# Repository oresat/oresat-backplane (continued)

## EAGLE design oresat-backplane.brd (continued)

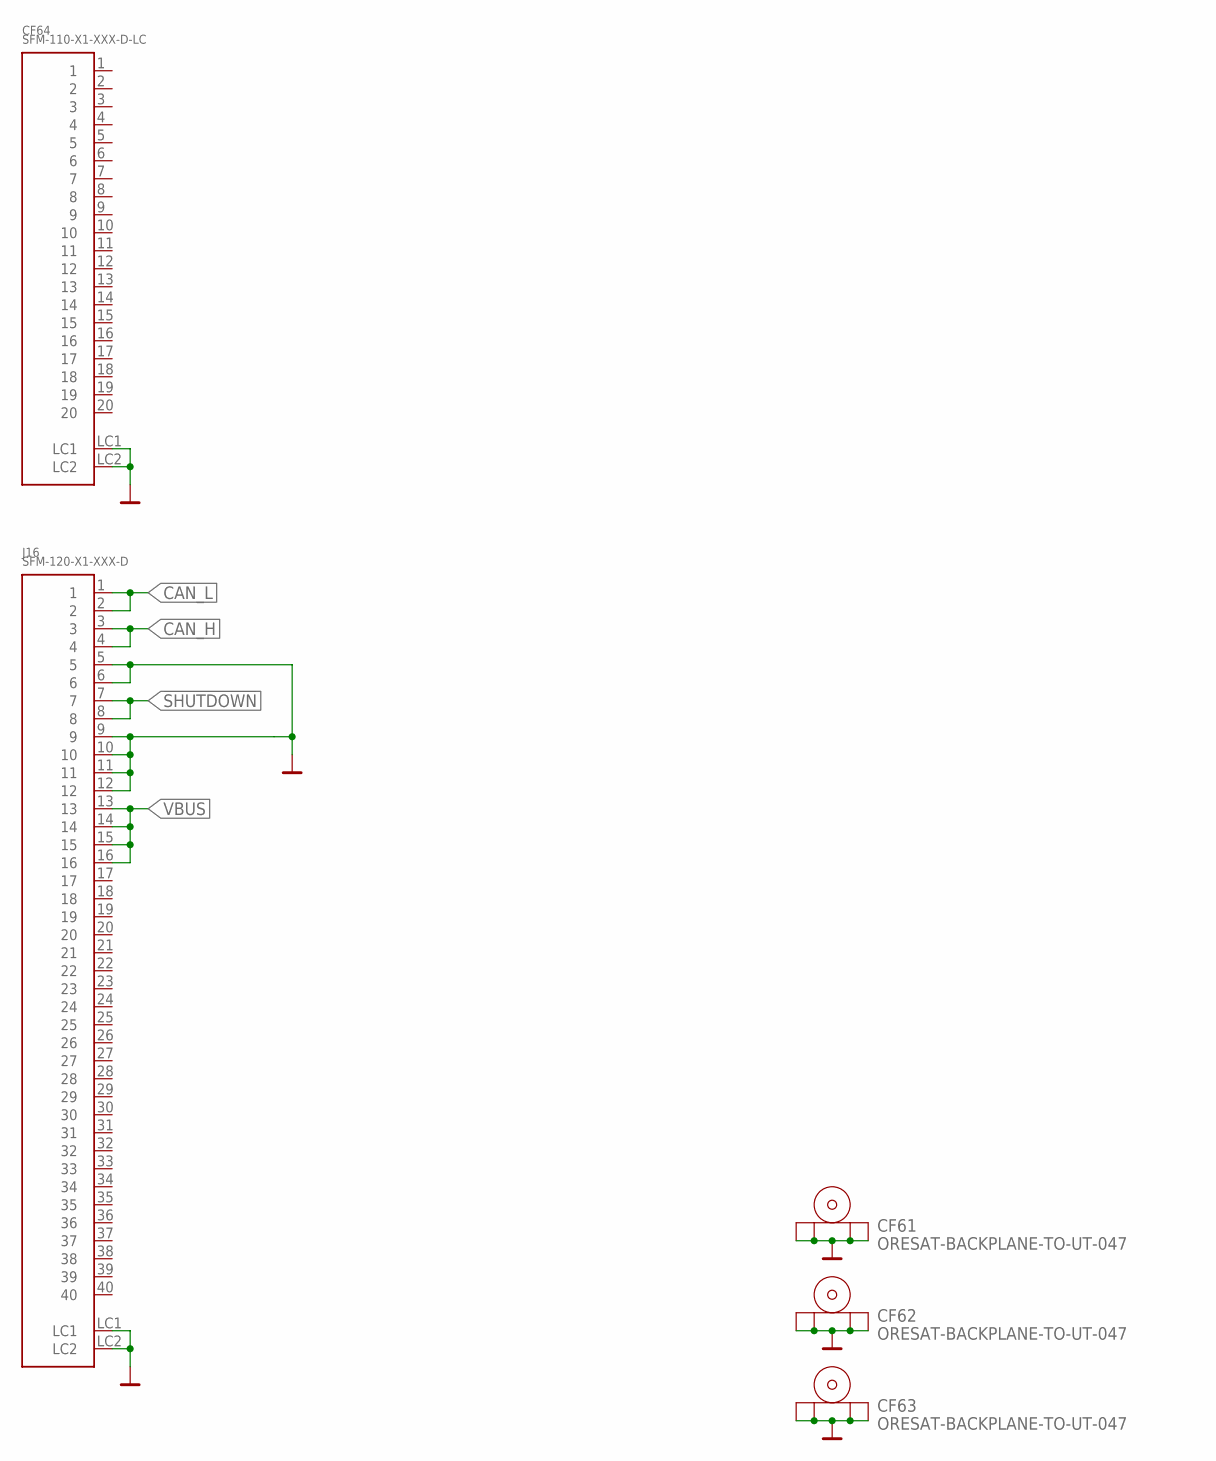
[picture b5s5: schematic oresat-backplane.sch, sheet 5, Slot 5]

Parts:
CF61, CF62, CF63: ORESAT-BACKPLANE-TO-UT-047; TEST
CF64: SFM-110-X1-XXX-D-LC
J16: SFM-120-X1-XXX-D

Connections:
!SHUTDOWN: J16.7, J16.8; also elsewhere on the board
CAN_H: J16.3, J16.4; also elsewhere on the board
CAN_L: J16.1, J16.2; also elsewhere on the board
GND: CF61.GND@1 (SHIELD), CF61.GND@2 (SHIELD1), CF61.GND@3 (SHIELD2), CF61.GND@4 (SHIELD3), CF62.GND@1 (SHIELD), CF62.GND@2 (SHIELD1), CF62.GND@3 (SHIELD2), CF62.GND@4 (SHIELD3), CF63.GND@1 (SHIELD), CF63.GND@2 (SHIELD1), CF63.GND@3 (SHIELD2), CF63.GND@4 (SHIELD3), CF64.LC1, CF64.LC2, J16.5, J16.6, J16.9, J16.10, J16.11, J16.12, J16.LC1, J16.LC2; also elsewhere on the board
VBUS: J16.13, J16.14, J16.15, J16.16; also elsewhere on the board

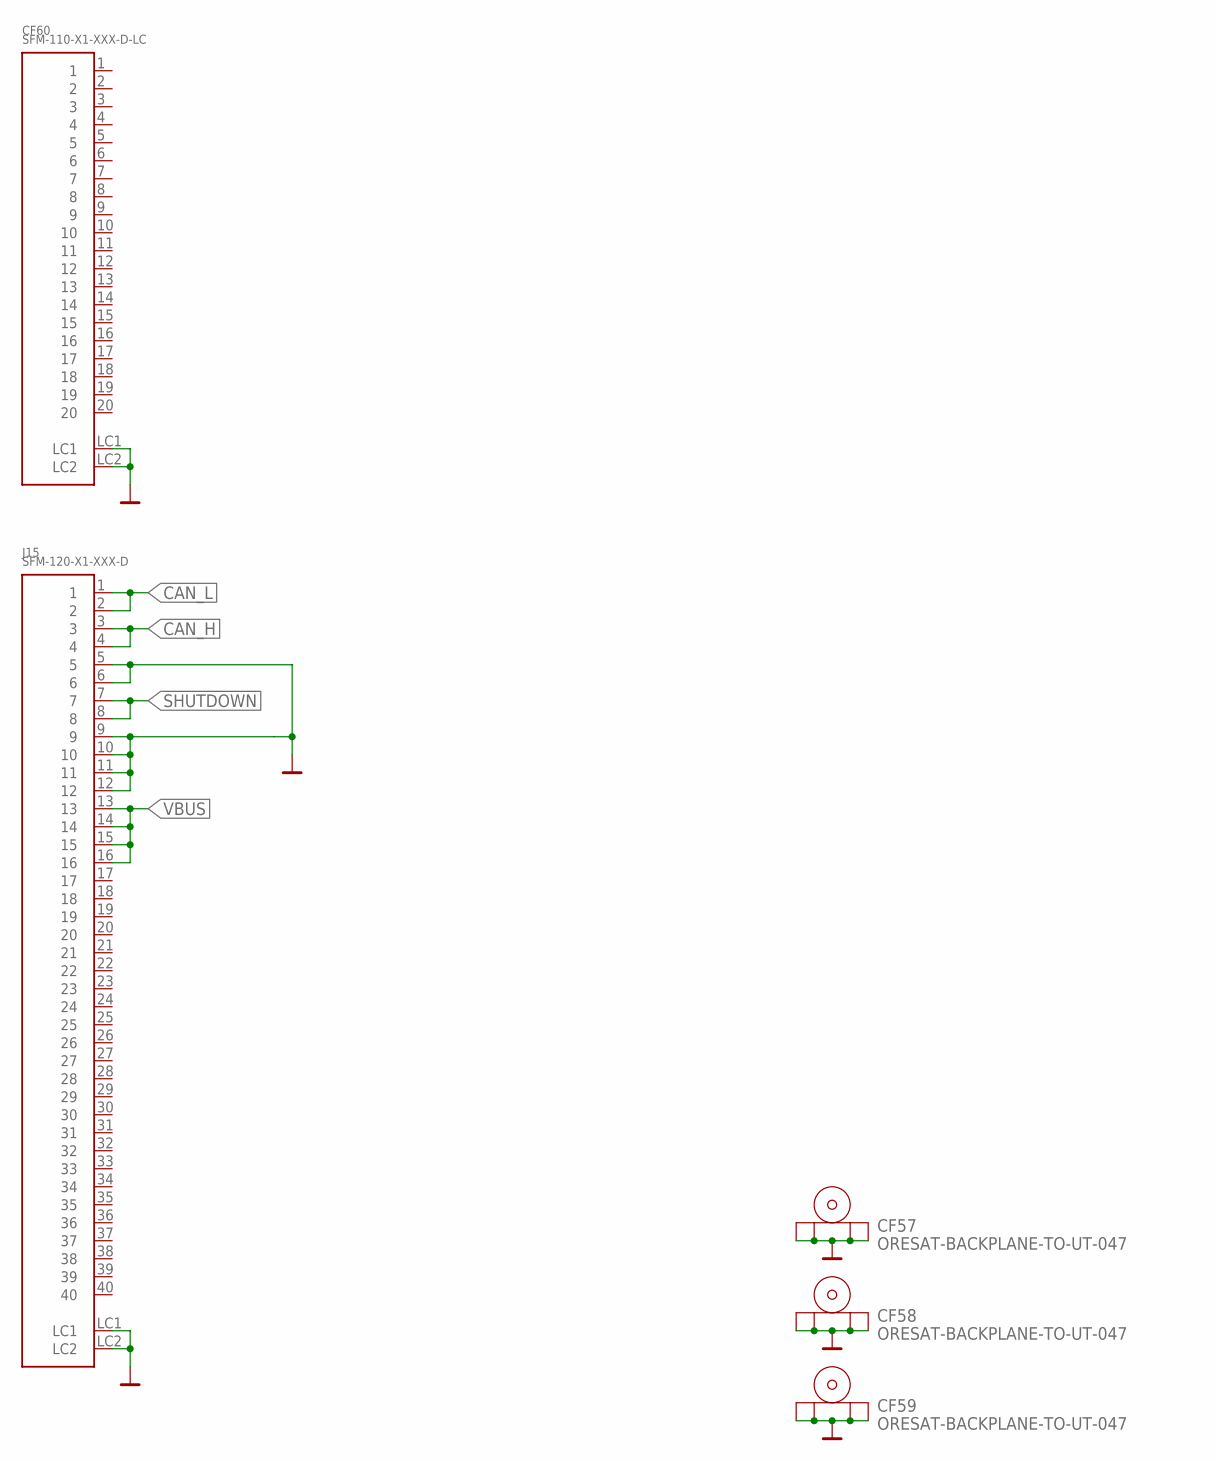
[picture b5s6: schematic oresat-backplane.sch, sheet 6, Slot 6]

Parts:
CF57, CF58, CF59: ORESAT-BACKPLANE-TO-UT-047; TEST
CF60: SFM-110-X1-XXX-D-LC
J15: SFM-120-X1-XXX-D

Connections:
!SHUTDOWN: J15.7, J15.8; also elsewhere on the board
CAN_H: J15.3, J15.4; also elsewhere on the board
CAN_L: J15.1, J15.2; also elsewhere on the board
GND: CF57.GND@1 (SHIELD), CF57.GND@2 (SHIELD1), CF57.GND@3 (SHIELD2), CF57.GND@4 (SHIELD3), CF58.GND@1 (SHIELD), CF58.GND@2 (SHIELD1), CF58.GND@3 (SHIELD2), CF58.GND@4 (SHIELD3), CF59.GND@1 (SHIELD), CF59.GND@2 (SHIELD1), CF59.GND@3 (SHIELD2), CF59.GND@4 (SHIELD3), CF60.LC1, CF60.LC2, J15.5, J15.6, J15.9, J15.10, J15.11, J15.12, J15.LC1, J15.LC2; also elsewhere on the board
VBUS: J15.13, J15.14, J15.15, J15.16; also elsewhere on the board

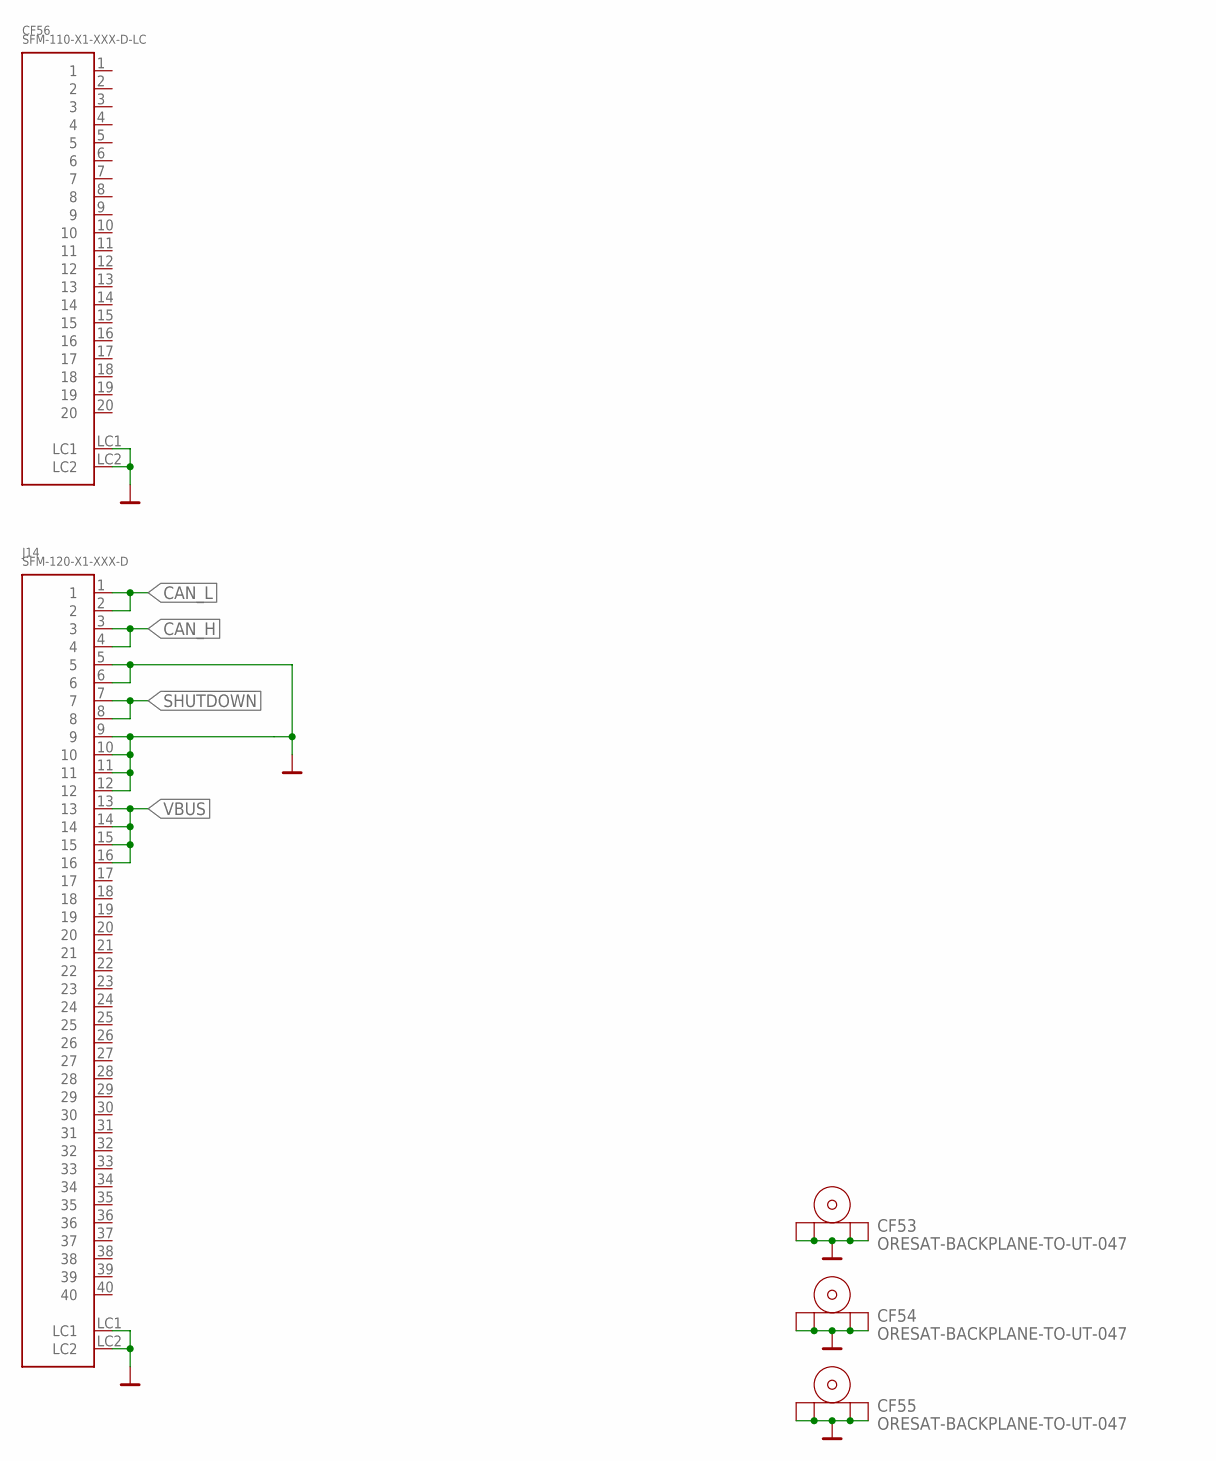
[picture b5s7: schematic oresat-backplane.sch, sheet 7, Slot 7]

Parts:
CF53, CF54, CF55: ORESAT-BACKPLANE-TO-UT-047; TEST
CF56: SFM-110-X1-XXX-D-LC
J14: SFM-120-X1-XXX-D

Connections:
!SHUTDOWN: J14.7, J14.8; also elsewhere on the board
CAN_H: J14.3, J14.4; also elsewhere on the board
CAN_L: J14.1, J14.2; also elsewhere on the board
GND: CF53.GND@1 (SHIELD), CF53.GND@2 (SHIELD1), CF53.GND@3 (SHIELD2), CF53.GND@4 (SHIELD3), CF54.GND@1 (SHIELD), CF54.GND@2 (SHIELD1), CF54.GND@3 (SHIELD2), CF54.GND@4 (SHIELD3), CF55.GND@1 (SHIELD), CF55.GND@2 (SHIELD1), CF55.GND@3 (SHIELD2), CF55.GND@4 (SHIELD3), CF56.LC1, CF56.LC2, J14.5, J14.6, J14.9, J14.10, J14.11, J14.12, J14.LC1, J14.LC2; also elsewhere on the board
VBUS: J14.13, J14.14, J14.15, J14.16; also elsewhere on the board

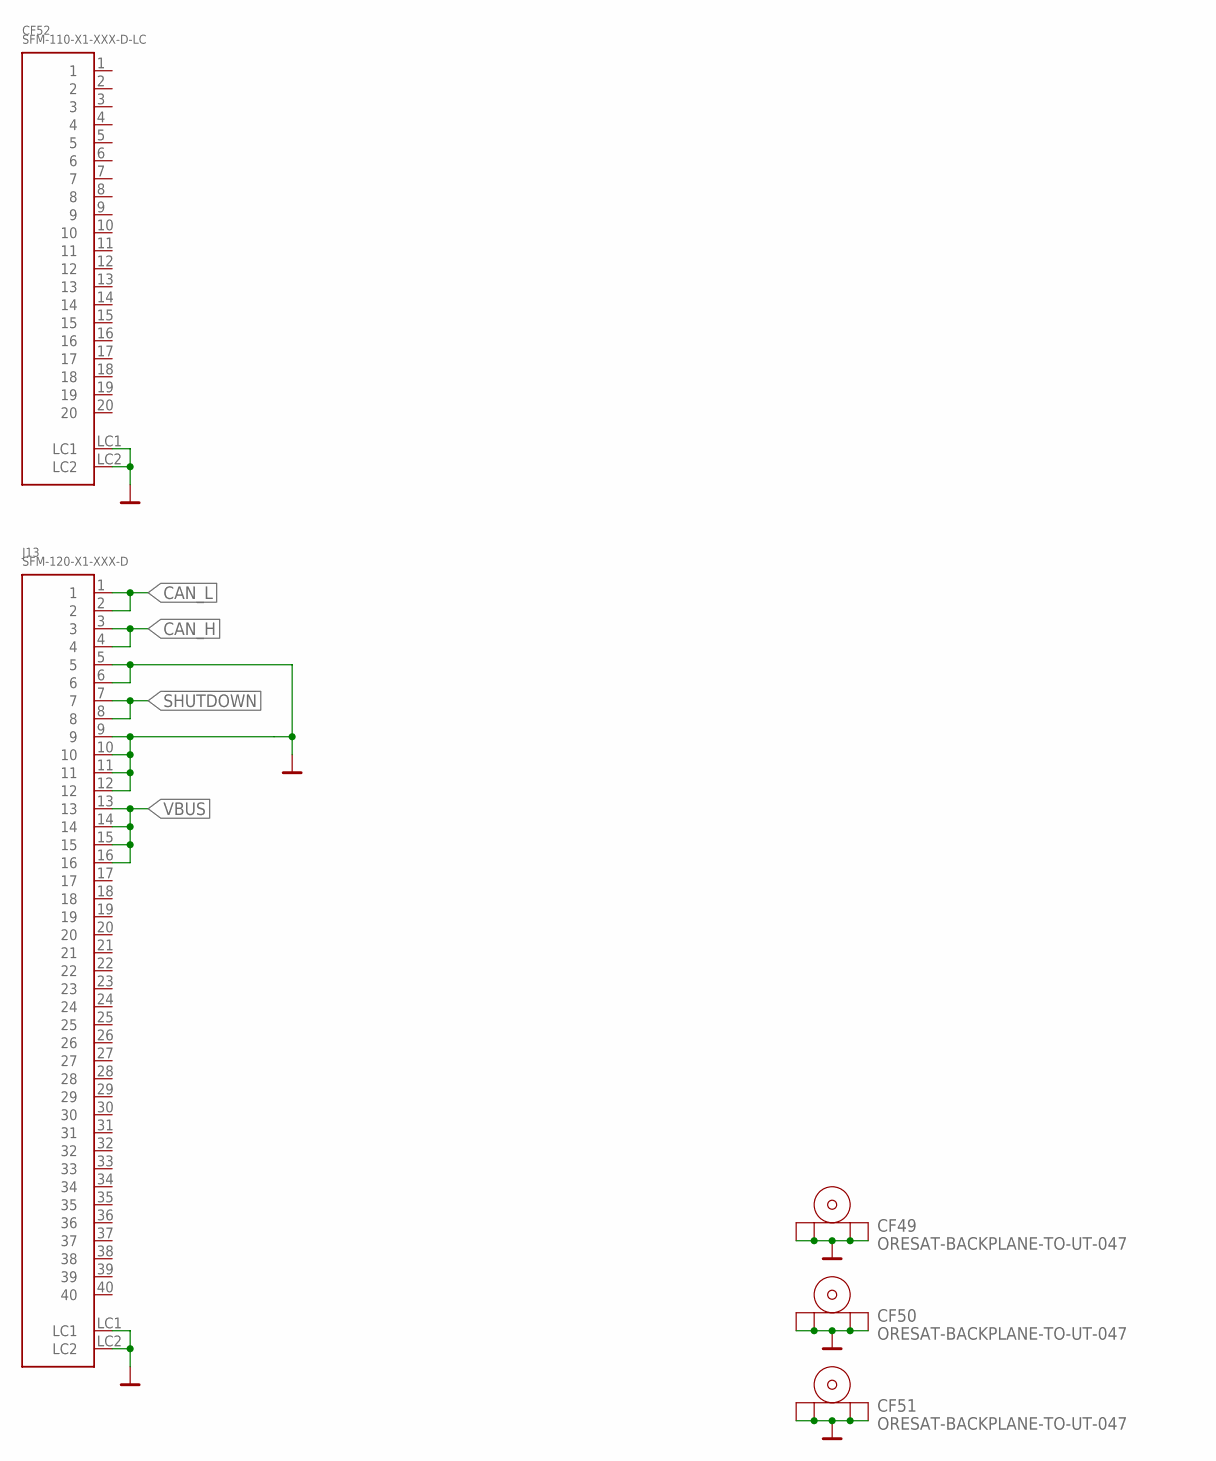
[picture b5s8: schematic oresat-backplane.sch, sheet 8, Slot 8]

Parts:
CF49, CF50, CF51: ORESAT-BACKPLANE-TO-UT-047; TEST
CF52: SFM-110-X1-XXX-D-LC
J13: SFM-120-X1-XXX-D

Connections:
!SHUTDOWN: J13.7, J13.8; also elsewhere on the board
CAN_H: J13.3, J13.4; also elsewhere on the board
CAN_L: J13.1, J13.2; also elsewhere on the board
GND: CF49.GND@1 (SHIELD), CF49.GND@2 (SHIELD1), CF49.GND@3 (SHIELD2), CF49.GND@4 (SHIELD3), CF50.GND@1 (SHIELD), CF50.GND@2 (SHIELD1), CF50.GND@3 (SHIELD2), CF50.GND@4 (SHIELD3), CF51.GND@1 (SHIELD), CF51.GND@2 (SHIELD1), CF51.GND@3 (SHIELD2), CF51.GND@4 (SHIELD3), CF52.LC1, CF52.LC2, J13.5, J13.6, J13.9, J13.10, J13.11, J13.12, J13.LC1, J13.LC2; also elsewhere on the board
VBUS: J13.13, J13.14, J13.15, J13.16; also elsewhere on the board

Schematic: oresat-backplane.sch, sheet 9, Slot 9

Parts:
CF45, CF46, CF47: ORESAT-BACKPLANE-TO-UT-047; TEST
CF48: SFM-110-X1-XXX-D-LC
J12: SFM-120-X1-XXX-D

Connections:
!SHUTDOWN: J12.7, J12.8; also elsewhere on the board
CAN_H: J12.3, J12.4; also elsewhere on the board
CAN_L: J12.1, J12.2; also elsewhere on the board
GND: CF45.GND@1 (SHIELD), CF45.GND@2 (SHIELD1), CF45.GND@3 (SHIELD2), CF45.GND@4 (SHIELD3), CF46.GND@1 (SHIELD), CF46.GND@2 (SHIELD1), CF46.GND@3 (SHIELD2), CF46.GND@4 (SHIELD3), CF47.GND@1 (SHIELD), CF47.GND@2 (SHIELD1), CF47.GND@3 (SHIELD2), CF47.GND@4 (SHIELD3), CF48.LC1, CF48.LC2, J12.5, J12.6, J12.9, J12.10, J12.11, J12.12, J12.LC1, J12.LC2; also elsewhere on the board
VBUS: J12.13, J12.14, J12.15, J12.16; also elsewhere on the board

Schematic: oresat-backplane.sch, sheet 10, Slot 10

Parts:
CF41, CF42, CF43: ORESAT-BACKPLANE-TO-UT-047; TEST
CF44: SFM-110-X1-XXX-D-LC
J11: SFM-120-X1-XXX-D

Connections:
!SHUTDOWN: J11.7, J11.8; also elsewhere on the board
CAN_H: J11.3, J11.4; also elsewhere on the board
CAN_L: J11.1, J11.2; also elsewhere on the board
GND: CF41.GND@1 (SHIELD), CF41.GND@2 (SHIELD1), CF41.GND@3 (SHIELD2), CF41.GND@4 (SHIELD3), CF42.GND@1 (SHIELD), CF42.GND@2 (SHIELD1), CF42.GND@3 (SHIELD2), CF42.GND@4 (SHIELD3), CF43.GND@1 (SHIELD), CF43.GND@2 (SHIELD1), CF43.GND@3 (SHIELD2), CF43.GND@4 (SHIELD3), CF44.LC1, CF44.LC2, J11.5, J11.6, J11.9, J11.10, J11.11, J11.12, J11.LC1, J11.LC2; also elsewhere on the board
VBUS: J11.13, J11.14, J11.15, J11.16; also elsewhere on the board

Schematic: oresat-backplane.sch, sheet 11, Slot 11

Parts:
CF37, CF38, CF39: ORESAT-BACKPLANE-TO-UT-047; TEST
CF40: SFM-110-X1-XXX-D-LC
J10: SFM-120-X1-XXX-D

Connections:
!SHUTDOWN: J10.7, J10.8; also elsewhere on the board
CAN_H: J10.3, J10.4; also elsewhere on the board
CAN_L: J10.1, J10.2; also elsewhere on the board
GND: CF37.GND@1 (SHIELD), CF37.GND@2 (SHIELD1), CF37.GND@3 (SHIELD2), CF37.GND@4 (SHIELD3), CF38.GND@1 (SHIELD), CF38.GND@2 (SHIELD1), CF38.GND@3 (SHIELD2), CF38.GND@4 (SHIELD3), CF39.GND@1 (SHIELD), CF39.GND@2 (SHIELD1), CF39.GND@3 (SHIELD2), CF39.GND@4 (SHIELD3), CF40.LC1, CF40.LC2, J10.5, J10.6, J10.9, J10.10, J10.11, J10.12, J10.LC1, J10.LC2; also elsewhere on the board
VBUS: J10.13, J10.14, J10.15, J10.16; also elsewhere on the board

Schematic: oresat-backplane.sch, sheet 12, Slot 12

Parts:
CF33, CF34, CF35: ORESAT-BACKPLANE-TO-UT-047; TEST
CF36: SFM-110-X1-XXX-D-LC
J9: SFM-120-X1-XXX-D

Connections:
!SHUTDOWN: J9.7, J9.8; also elsewhere on the board
CAN_H: J9.3, J9.4; also elsewhere on the board
CAN_L: J9.1, J9.2; also elsewhere on the board
GND: CF33.GND@1 (SHIELD), CF33.GND@2 (SHIELD1), CF33.GND@3 (SHIELD2), CF33.GND@4 (SHIELD3), CF34.GND@1 (SHIELD), CF34.GND@2 (SHIELD1), CF34.GND@3 (SHIELD2), CF34.GND@4 (SHIELD3), CF35.GND@1 (SHIELD), CF35.GND@2 (SHIELD1), CF35.GND@3 (SHIELD2), CF35.GND@4 (SHIELD3), CF36.LC1, CF36.LC2, J9.5, J9.6, J9.9, J9.10, J9.11, J9.12, J9.LC1, J9.LC2; also elsewhere on the board
VBUS: J9.13, J9.14, J9.15, J9.16; also elsewhere on the board

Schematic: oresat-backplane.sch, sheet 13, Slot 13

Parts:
CF29, CF30, CF31: ORESAT-BACKPLANE-TO-UT-047; TEST
CF32: SFM-110-X1-XXX-D-LC
J8: SFM-120-X1-XXX-D

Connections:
!SHUTDOWN: J8.7, J8.8; also elsewhere on the board
CAN_H: J8.3, J8.4; also elsewhere on the board
CAN_L: J8.1, J8.2; also elsewhere on the board
GND: CF29.GND@1 (SHIELD), CF29.GND@2 (SHIELD1), CF29.GND@3 (SHIELD2), CF29.GND@4 (SHIELD3), CF30.GND@1 (SHIELD), CF30.GND@2 (SHIELD1), CF30.GND@3 (SHIELD2), CF30.GND@4 (SHIELD3), CF31.GND@1 (SHIELD), CF31.GND@2 (SHIELD1), CF31.GND@3 (SHIELD2), CF31.GND@4 (SHIELD3), CF32.LC1, CF32.LC2, J8.5, J8.6, J8.9, J8.10, J8.11, J8.12, J8.LC1, J8.LC2; also elsewhere on the board
VBUS: J8.13, J8.14, J8.15, J8.16; also elsewhere on the board

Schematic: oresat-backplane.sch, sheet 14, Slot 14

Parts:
CF25, CF26, CF27: ORESAT-BACKPLANE-TO-UT-047; TEST
CF28: SFM-110-X1-XXX-D-LC
J7: SFM-120-X1-XXX-D

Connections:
!SHUTDOWN: J7.7, J7.8; also elsewhere on the board
CAN_H: J7.3, J7.4; also elsewhere on the board
CAN_L: J7.1, J7.2; also elsewhere on the board
GND: CF25.GND@1 (SHIELD), CF25.GND@2 (SHIELD1), CF25.GND@3 (SHIELD2), CF25.GND@4 (SHIELD3), CF26.GND@1 (SHIELD), CF26.GND@2 (SHIELD1), CF26.GND@3 (SHIELD2), CF26.GND@4 (SHIELD3), CF27.GND@1 (SHIELD), CF27.GND@2 (SHIELD1), CF27.GND@3 (SHIELD2), CF27.GND@4 (SHIELD3), CF28.LC1, CF28.LC2, J7.5, J7.6, J7.9, J7.10, J7.11, J7.12, J7.LC1, J7.LC2; also elsewhere on the board
VBUS: J7.13, J7.14, J7.15, J7.16; also elsewhere on the board

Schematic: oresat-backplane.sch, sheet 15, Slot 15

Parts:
CF21, CF22, CF23: ORESAT-BACKPLANE-TO-UT-047; TEST
CF24: SFM-110-X1-XXX-D-LC
J6: SFM-120-X1-XXX-D

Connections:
!SHUTDOWN: J6.7, J6.8; also elsewhere on the board
CAN_H: J6.3, J6.4; also elsewhere on the board
CAN_L: J6.1, J6.2; also elsewhere on the board
GND: CF21.GND@1 (SHIELD), CF21.GND@2 (SHIELD1), CF21.GND@3 (SHIELD2), CF21.GND@4 (SHIELD3), CF22.GND@1 (SHIELD), CF22.GND@2 (SHIELD1), CF22.GND@3 (SHIELD2), CF22.GND@4 (SHIELD3), CF23.GND@1 (SHIELD), CF23.GND@2 (SHIELD1), CF23.GND@3 (SHIELD2), CF23.GND@4 (SHIELD3), CF24.LC1, CF24.LC2, J6.5, J6.6, J6.9, J6.10, J6.11, J6.12, J6.LC1, J6.LC2; also elsewhere on the board
VBUS: J6.13, J6.14, J6.15, J6.16; also elsewhere on the board

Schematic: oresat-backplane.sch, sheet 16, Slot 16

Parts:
CF17, CF18, CF19: ORESAT-BACKPLANE-TO-UT-047; TEST
CF20: SFM-110-X1-XXX-D-LC
J5: SFM-120-X1-XXX-D

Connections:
!SHUTDOWN: J5.7, J5.8; also elsewhere on the board
CAN_H: J5.3, J5.4; also elsewhere on the board
CAN_L: J5.1, J5.2; also elsewhere on the board
GND: CF17.GND@1 (SHIELD), CF17.GND@2 (SHIELD1), CF17.GND@3 (SHIELD2), CF17.GND@4 (SHIELD3), CF18.GND@1 (SHIELD), CF18.GND@2 (SHIELD1), CF18.GND@3 (SHIELD2), CF18.GND@4 (SHIELD3), CF19.GND@1 (SHIELD), CF19.GND@2 (SHIELD1), CF19.GND@3 (SHIELD2), CF19.GND@4 (SHIELD3), CF20.LC1, CF20.LC2, J5.5, J5.6, J5.9, J5.10, J5.11, J5.12, J5.LC1, J5.LC2; also elsewhere on the board
VBUS: J5.13, J5.14, J5.15, J5.16; also elsewhere on the board

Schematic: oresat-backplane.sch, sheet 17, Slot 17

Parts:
CF13, CF14, CF15: ORESAT-BACKPLANE-TO-UT-047; TEST
CF16: SFM-110-X1-XXX-D-LC
J4: SFM-120-X1-XXX-D

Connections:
!SHUTDOWN: J4.7, J4.8; also elsewhere on the board
CAN_H: J4.3, J4.4; also elsewhere on the board
CAN_L: J4.1, J4.2; also elsewhere on the board
GND: CF13.GND@1 (SHIELD), CF13.GND@2 (SHIELD1), CF13.GND@3 (SHIELD2), CF13.GND@4 (SHIELD3), CF14.GND@1 (SHIELD), CF14.GND@2 (SHIELD1), CF14.GND@3 (SHIELD2), CF14.GND@4 (SHIELD3), CF15.GND@1 (SHIELD), CF15.GND@2 (SHIELD1), CF15.GND@3 (SHIELD2), CF15.GND@4 (SHIELD3), CF16.LC1, CF16.LC2, J4.5, J4.6, J4.9, J4.10, J4.11, J4.12, J4.LC1, J4.LC2; also elsewhere on the board
VBUS: J4.13, J4.14, J4.15, J4.16; also elsewhere on the board

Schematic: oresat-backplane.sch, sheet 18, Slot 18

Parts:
CF9, CF10, CF11: ORESAT-BACKPLANE-TO-UT-047; TEST
CF12: SFM-110-X1-XXX-D-LC
J3: SFM-120-X1-XXX-D

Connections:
!SHUTDOWN: J3.7, J3.8; also elsewhere on the board
CAN_H: J3.3, J3.4; also elsewhere on the board
CAN_L: J3.1, J3.2; also elsewhere on the board
GND: CF9.GND@1 (SHIELD), CF9.GND@2 (SHIELD1), CF9.GND@3 (SHIELD2), CF9.GND@4 (SHIELD3), CF10.GND@1 (SHIELD), CF10.GND@2 (SHIELD1), CF10.GND@3 (SHIELD2), CF10.GND@4 (SHIELD3), CF11.GND@1 (SHIELD), CF11.GND@2 (SHIELD1), CF11.GND@3 (SHIELD2), CF11.GND@4 (SHIELD3), CF12.LC1, CF12.LC2, J3.5, J3.6, J3.9, J3.10, J3.11, J3.12, J3.LC1, J3.LC2; also elsewhere on the board
VBUS: J3.13, J3.14, J3.15, J3.16; also elsewhere on the board

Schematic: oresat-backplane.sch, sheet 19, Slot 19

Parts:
CF4, CF5, CF6: ORESAT-BACKPLANE-TO-UT-047; TEST
CF7: SFM-110-X1-XXX-D-LC
J2: SFM-120-X1-XXX-D

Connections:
!SHUTDOWN: J2.7, J2.8; also elsewhere on the board
CAN_H: J2.3, J2.4; also elsewhere on the board
CAN_L: J2.1, J2.2; also elsewhere on the board
GND: CF4.GND@1 (SHIELD), CF4.GND@2 (SHIELD1), CF4.GND@3 (SHIELD2), CF4.GND@4 (SHIELD3), CF5.GND@1 (SHIELD), CF5.GND@2 (SHIELD1), CF5.GND@3 (SHIELD2), CF5.GND@4 (SHIELD3), CF6.GND@1 (SHIELD), CF6.GND@2 (SHIELD1), CF6.GND@3 (SHIELD2), CF6.GND@4 (SHIELD3), CF7.LC1, CF7.LC2, J2.5, J2.6, J2.9, J2.10, J2.11, J2.12, J2.LC1, J2.LC2; also elsewhere on the board
VBUS: J2.13, J2.14, J2.15, J2.16; also elsewhere on the board

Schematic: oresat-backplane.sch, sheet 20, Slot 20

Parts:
CF1, CF2, CF3: ORESAT-BACKPLANE-TO-UT-047; TEST
CF8: SFM-110-X1-XXX-D-LC

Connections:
GND: CF1.GND@1 (SHIELD), CF1.GND@2 (SHIELD1), CF1.GND@3 (SHIELD2), CF1.GND@4 (SHIELD3), CF2.GND@1 (SHIELD), CF2.GND@2 (SHIELD1), CF2.GND@3 (SHIELD2), CF2.GND@4 (SHIELD3), CF3.GND@1 (SHIELD), CF3.GND@2 (SHIELD1), CF3.GND@3 (SHIELD2), CF3.GND@4 (SHIELD3), CF8.LC1, CF8.LC2; also elsewhere on the board

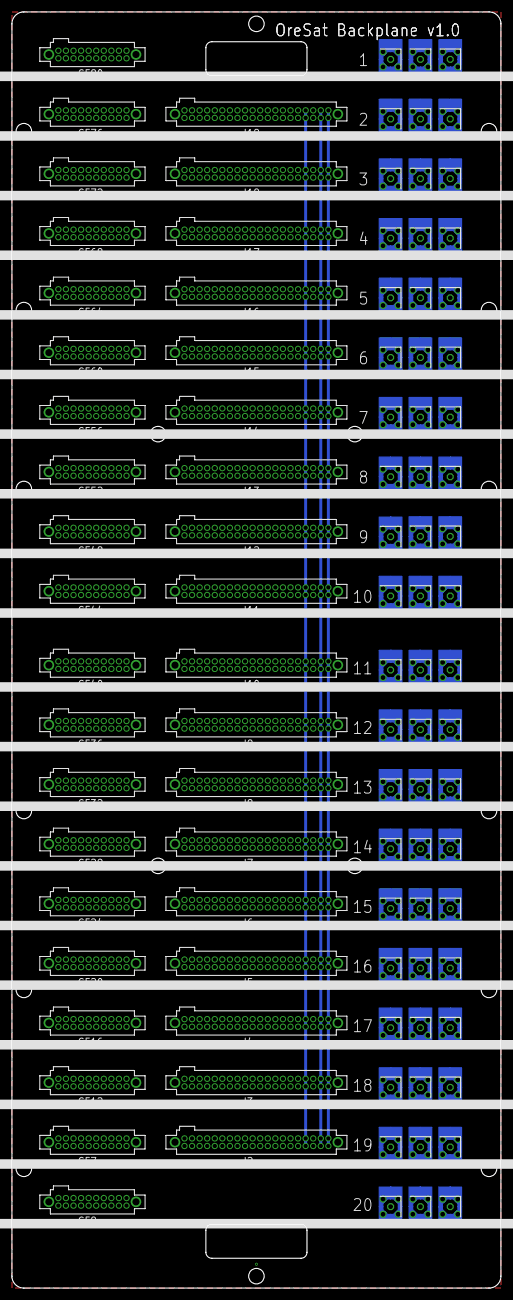
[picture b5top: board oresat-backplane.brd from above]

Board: 2 copper layers, 82.0 x 214.0 mm, 98 parts (0 on the bottom side), 5 nets.

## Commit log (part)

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2016-03-11 README file
2016-03-11 initial commit with board outline, holes, and first three connectors
2016-03-26 Updated backplane to latest connectors - 1.27 mm 2x20 and new MCX connectors. Also added keep outs from Jeremy.
2016-03-26 Updated to TE MCX M verticals to save precious, precious mm on the cards
2018-08-19 Latest backplane, with SamTec TigerEye SFM-1x0 connectors, and with MMCX to UT-047 RF connectors.
2018-08-19 Beginnings of the 20 slots, with connectors! Almost Joe Approved, waiting for better DXF.
2018-08-20 OMG we have a backplane. Note that the MMCX connectors are probably incorrectly placed because we're going to switch to some different connector that's more SMT-y for Oliver because he's an RF racist.
2018-09-11 Backplane v1.0. Finally. Uses SMPM RF connectors.
2018-09-11 Added connector specs to the README file.
2018-09-11 Added .gitignore file.
2018-09-17 Updated center fasteners with new precision shoulder bolt diameter and spring-like arm.
2018-10-02 Version 1.0 of backplane. With SMPM connectors, with the correct BSTOP layer for thermal connection to the -X frame, and with separate pins on the backplane connectors for future flexibility in this 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
2018-10-02 Ground stitching. Probably don't need it, but...
2018-10-02 Updated README with image and added explicit license.
2018-10-02 Fixed formatting.
2018-10-02 Minor cleanup.
2018-10-02 Added aux conncetor info.
2018-10-02 OOps, need a BOM.
2018-12-03 Updated TFM connectors with smaller holes and bigger pads based on the v1.0 backplane. Now it's V1.1!
2019-01-15 Backplane v1.1. Main connectors to all cards including end cards, Aux connector to all cards but the end card, signals named, etc.
2019-01-15 Oh right, stitching on the ends.
2019-01-15 Updated picture and readme.
2019-02-22 Fixed wrong signal names, removed thermals from bottom of main connectors, should be ready for fab.
2019-05-26 Backplane v3. All good, except for the polygon error that keeps killing EAGLE. I thought this was fixed? Also, the RF stuff is all terrible until Vigely fixgures out what we should do :)
2019-06-20 Updated connector locations from MCAD. Last of the separate RF grounds before reverting back to single ground plane.
2019-06-29 Backplane v2.0! New dimensions and connector placement for Frame v1.1. New bespoke RF lines for the current OreSat RF card and antenna plan. After design review, added one more pin pair to vbus and g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
2019-06-29 Updated microstrips to 0.38 mm based on theoretical calcs of 0.35 mm for the OSH Park 4 layer, and Harmon Industry's measurements of 0.41 mm for 50 ohms. Also expanded solder mask openings around RF 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
2019-07-01 Last polish before fab. Removed copper and solder mask from the fasteners that don't make electrical contact, so they can be cycled without flaking and other damage.
2019-07-24 Updated to latest backplane DXF. Reduced all sides by 0.15 mm. Fixed solar connector cutout areas that were lopsided. Awaiting RF testing.
2019-08-20 "auto-generated from update_repos.py"
2019-11-01 added oresat grounding block diagram
2020-02-16 More additions to v2.1: split termination on the CAN busses, locked everything down, and moved the RF connectors to where they're currently supposed to be.
2020-02-16 Updated BOM for v2.1.
2020-07-13 Created OreSat0 1U backplane from 2U backplane.
2020-07-13 Widended shoulder bolt screw down area to cover the entire bolt. Shouldn't affect anything.
2020-07-13 oresat-backplane-1u.sch
2020-07-13 Uh, whoops, should have committed these at the same time. First draft of the 1U backplane. Passes ERC and DRC.
2020-07-20 TNAMES cleanup, renamed by card number.
2020-08-01 Cleaned up README and BOMs for 1U and 2U backplanes.
2020-08-26 Added 1U -Z end cap connector.
2020-08-26 Added -Z end cap connector to 1U
2020-08-28 Backplane v1.1!
2020-11-17 Updated 1U backplane to v1.2. Better position of end cap connector, added debug connector.
2020-12-08 Final tweaks to v1.2 - off to fab.
2020-12-08 Updated with corrected debug connector. Footprint didn't change, so no change to version.
2020-12-09 First cut of the debug port hat.
2020-12-11 Added debug connector to 1U BOM.
2020-12-11 First rev of debug port breakout.
2021-03-22 Version 1.3. No significant difference with v1.2 besides added TPLACE block, updated not for flight marker, and fiducials just in case.
2021-03-22 v1.1 debug port breakout. v1.0 wasn't deep enough so it hit the solar panel.
2021-03-22 v1.1 of the debug port plug. Perhaps it's not a great to short out literally every pin on the bus to ground? Maybe?
2021-10-03 Backplane v2.0. Changes to signals; vaguely back compatible with v1. Also spun off OreSat0 bespoke backplane for the OreSat0 mission.
2021-10-18 Final OreSat0 1U backplane and new BOM.
2021-11-03 OreSat0 1U backplane; as manufacutred 2021-11-01
2021-11-11 Minor BOM formatting.
2021-11-11 Updated spare lines in schematic to reflect magnetometer usage; no change to board.
2022-02-06 Repo cleanup since we're moving to KiCAD, and sorting by U.
2022-02-06 Half-done changes to the 2U (needs fixing, but in KiCAD).
2022-02-06 Add HASP mission backplane (never used).
2022-02-06 Added note on HASP, added CERN OHL 2.
2022-02-06 REmoved 1U v1.1 debug port; moved to flatsat repo.
2022-02-06 Added debug connector information.
2022-02-06 Updated PNG of 1U to OreSat0!
2022-06-29 Moved 2u-hasp backplane to KiCad
2022-06-29 Fixed microstrip clearance
2022-07-06 Migrated 1u to KiCad
2022-07-07 Moved the correct 2u backplane to KiCad this time
2022-07-13 RF traces are fixed, hopefully correctly
2022-07-15 Made the DRC happy with better RF footprints
2022-07-15 Fixed symbol library
2022-07-18 Fixed DRC errors and warnings
2022-07-27 Rearranged the RF connectors for Oresat0.5
2022-07-27 Updated 2u backplane connector stuff
2022-07-27 Fixed RF traces and connectors, and DRC
2022-07-27 Updated silkscreen to use layout title
2022-07-27 Changed title block
2022-07-29 Aligned everything to the DXF, should maybe be done I think
2023-02-19 Big reorg for OreSat0.5, update .gitignore.
2023-02-19 Created Oresat0.5 backplane
2023-02-19 Added end mounting holes and CAN connector resistors
2023-02-19 Fixed all (most) of the issues from Eagle imports
2023-02-19 Moved entire schematic to single page
2023-02-19 Cleaned up OreSat0.5 backplane folder
2023-02-20 Fixed backplane connector library names
2023-02-20 Fixed silkscreen on copper
2023-02-20 Updated 2U DXF to something more useful, and rename Ben's naming faux pas.
2023-02-20 Removing unecessary files.
2023-02-20 Update CAM settings for building Gerbers.
2023-03-28 Added S/N block and updated to KiCad7
2023-03-28 Moved aux connectors, fixed RF connector soldermask
2023-04-23 Removed soldermask around mounting screws
2023-04-25 Polished v1.1 of the OreSat0.5 backplane: fixed schematic off grid issues and updated symbols, removed copper spikes, updated date, ignored ignorable DRC errors.
2025-09-29 New OreSat1 2U backplane. Switched to the correct backplane design (OreSat0.5 was incorrect) and broke up into multiple sheets. Set actual part numbers for BOM, added symbols for fastener holes. Stil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
2025-10-04 Started 3U design
2025-10-05 Most current version
2025-10-05 Fixed
2025-10-08 Rough draft
    Lots more cleaning up to be done
2025-10-09 Update of OreSat1 2U backplane. Removed extraneous connectors, imported DXF from OnShape and moved debug connectors by 0.176 mm. Routing left to do.
2025-10-14 Updated DXF to latest (still no solder mask) and finished routing based on new card placements.
2025-10-21 Most up to date
2025-10-22 Added latest DXF drawing from the structure team, updated the stackup with OreSat standards, updated the page sizes, etc.
2025-10-22 Actually commit all of the files created for the scheamtic :/
2025-10-22 Remove zip file
2025-10-22 Fixed libraries and footprints, synced sch and pcb (sorry Jacob).
2025-10-22 Fix library issues on aux footprints.
2025-10-22 Added example aux connectors.
2025-11-21 Connectors placed & zoned
2025-11-21 Added more Auxiliary connectors
2025-11-23 Connectors laid out, unrouted
2025-11-23 Update .gitignore file with autosave temp file.
2025-11-30 Added traces between main connectors, RF cons labelled, vbus zones set
2025-12-02 Fixed DRC errors
2025-12-02 Moved can lines to back & fixed RF schematic organization
2025-12-04 Can lines on back - need to move can resistors to front & add b.side solder mask
2025-12-04 Back solder mask added & can resistors moved to F.cu. Final
2025-12-04 Disconnected RF DRC violations excluded
2025-12-29 OreSat1 backplane v1.0 commit
    Final cleanup. moved should bolt holes from to drilled holes, not routed holes. Updated date on schematic and board. Sending out for fab.
2026-02-07 Removed deployables and turned them into spares.
2026-02-21 new dir w ESI changes v1
    may need to redo RF
2026-02-21 Added schematic and board variables, polished some silkscreen, reviewed board, renamed directory
2026-02-21 Added fastener solder mask cutouts and copper keep out zones for all fasteners.
2026-02-21 Updated generic 3U backplane with correct fastener copper and solder mask cutouts under fastners, and updated date on sch and brd.
2026-02-21 Removed refdes for holes. Silly.
2026-02-22 Labelled connectors & disconnected C3 LBand
2026-02-22 fixed erc and drc errors
2026-02-22 changed file org
2026-02-22 Polish of 3U for ESI
    Fixed ERC/DRC/sync errors. Made fancy RF table. Fixed BOM.
2026-02-22 Update date!
2026-02-22 Cleaned up the files Shae was trying to clean up
2026-02-22 Add some automation to the 3U build
2026-02-22 Better documentation on Makefile
2026-02-22 OreSat1 backplane v1.1
    Lots of little changes; technically there should be no actual changes betwen v1.0 and v1.1 but
    the BOM is correct, the masks are done better, the precision shoulder bolts are drills not
    routed, and it's just cleaned up a lot.
2026-02-22 Upgrade makefile; now fully automatic, finds the local project name
2026-02-22 Upgrade makefile to latest and changed bom presets to match
2026-02-24 Adding DXF of 3U backplane
2026-02-26 ESI backplane edge cut changes & naming changes
2026-02-27 updated microstrips around cutout
2026-02-27 Final polishing of ESI backplane and updated Makefile
2026-03-05 Changed schematic & pcb to add spare traces, no helical or turnstile
2026-03-05 Update makefile
2026-03-05 Changed DNP for SDR control board
2026-03-06 Renamed ESI backplane
2026-03-09 Version 1.1 of the ESI OreSat backplane
    Lots of cleanup for the automated build, including adding READMEs and fiducials! Ready for fab!
2026-03-09 Small fix for CAD directory
2026-03-09 Zip the CAD file too
2026-03-09 build file and updated footprints
2026-03-09 footprint weirdness fixed
2026-03-09 fixed resistor footprint issues?
2026-03-12 Fixed minor BOM issue with a repeated connector.
2026-03-12 Minor BOM fix on 2U
2026-03-12 Updated makefile
2026-04-01 Switch C3 and SBand card, GPS now under C3 -- Needs review
2026-04-03 Added solder paste to RF Connectors
2026-04-05 updated spare lines on schematic & began tracing
    a little more than halfway through
2026-04-05 More routing
2026-04-06 Board switches and microstrip mask change
2026-04-08 Moved RW and mag cards back, changes spare tracing side -- updated DNP w changes
2026-04-08 Fix and update SMPM connectors, now they're sane for KiCad. Also, move to DRU-based ground plane peelback to avoid DRC errors, and improve fmask layer. Also lock a bunch of stuff that ought to be loc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
2026-04-08 minor f mask fix around SMPMs
2026-04-09 more stitching, updated date, updated makefile and README
2026-04-09 Star tracker connect added, got rid of SDR
2026-04-26 Connected Spares and switched OPD to inner layer. Updated RF cons -- **RF con new footprint has ground pad schematic parity error
2026-04-26 Updated schematic symbol for RF con. Believe this is done. Remaining DRC errors are only unconnected RF cons -- fine until use defined for non-generic version.
2026-04-26 remove .history files
